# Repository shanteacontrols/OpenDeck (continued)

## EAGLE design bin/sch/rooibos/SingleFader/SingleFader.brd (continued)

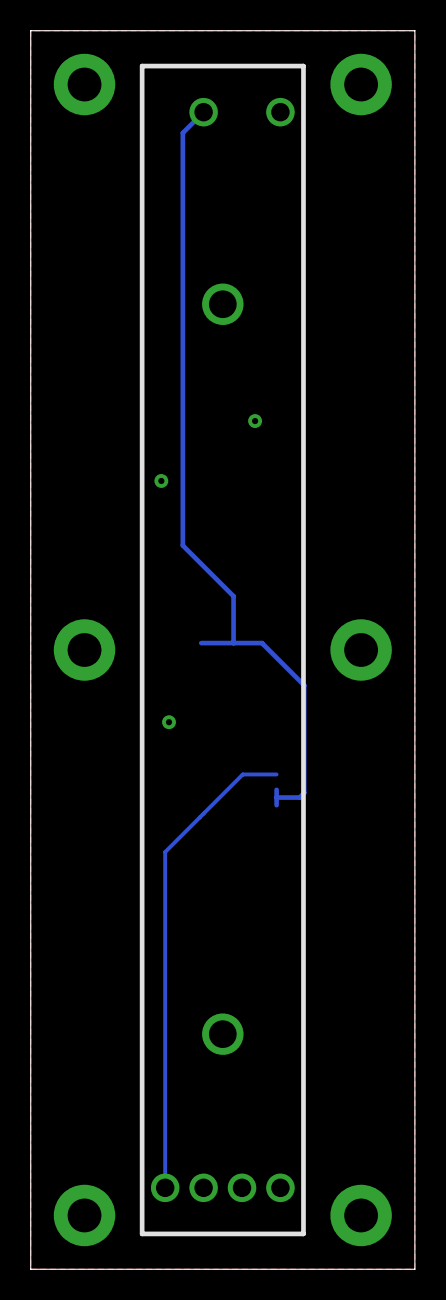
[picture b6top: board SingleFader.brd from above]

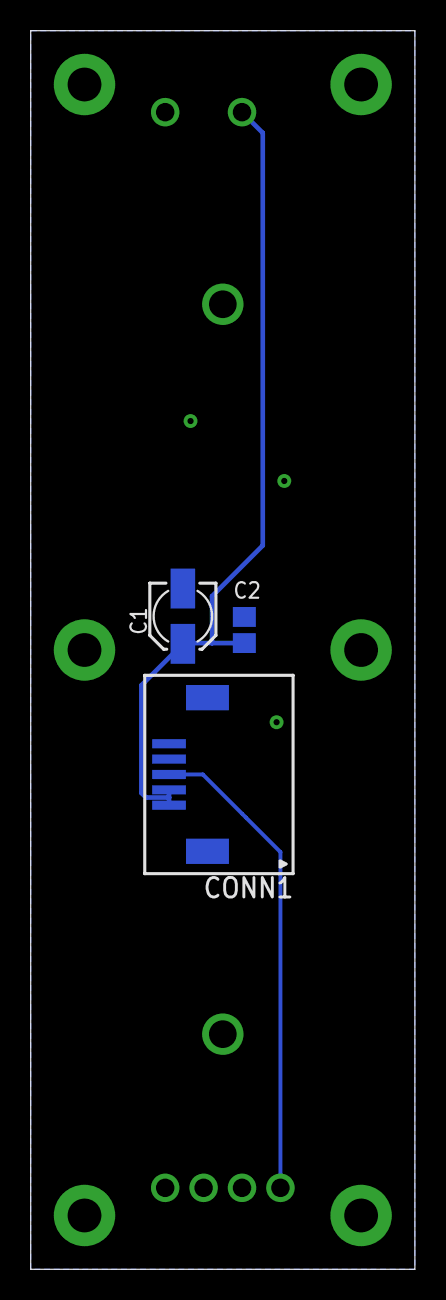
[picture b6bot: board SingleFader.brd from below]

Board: 2 copper layers, 25.0 x 80.6 mm, 4 parts (3 on the bottom side), 3 nets.

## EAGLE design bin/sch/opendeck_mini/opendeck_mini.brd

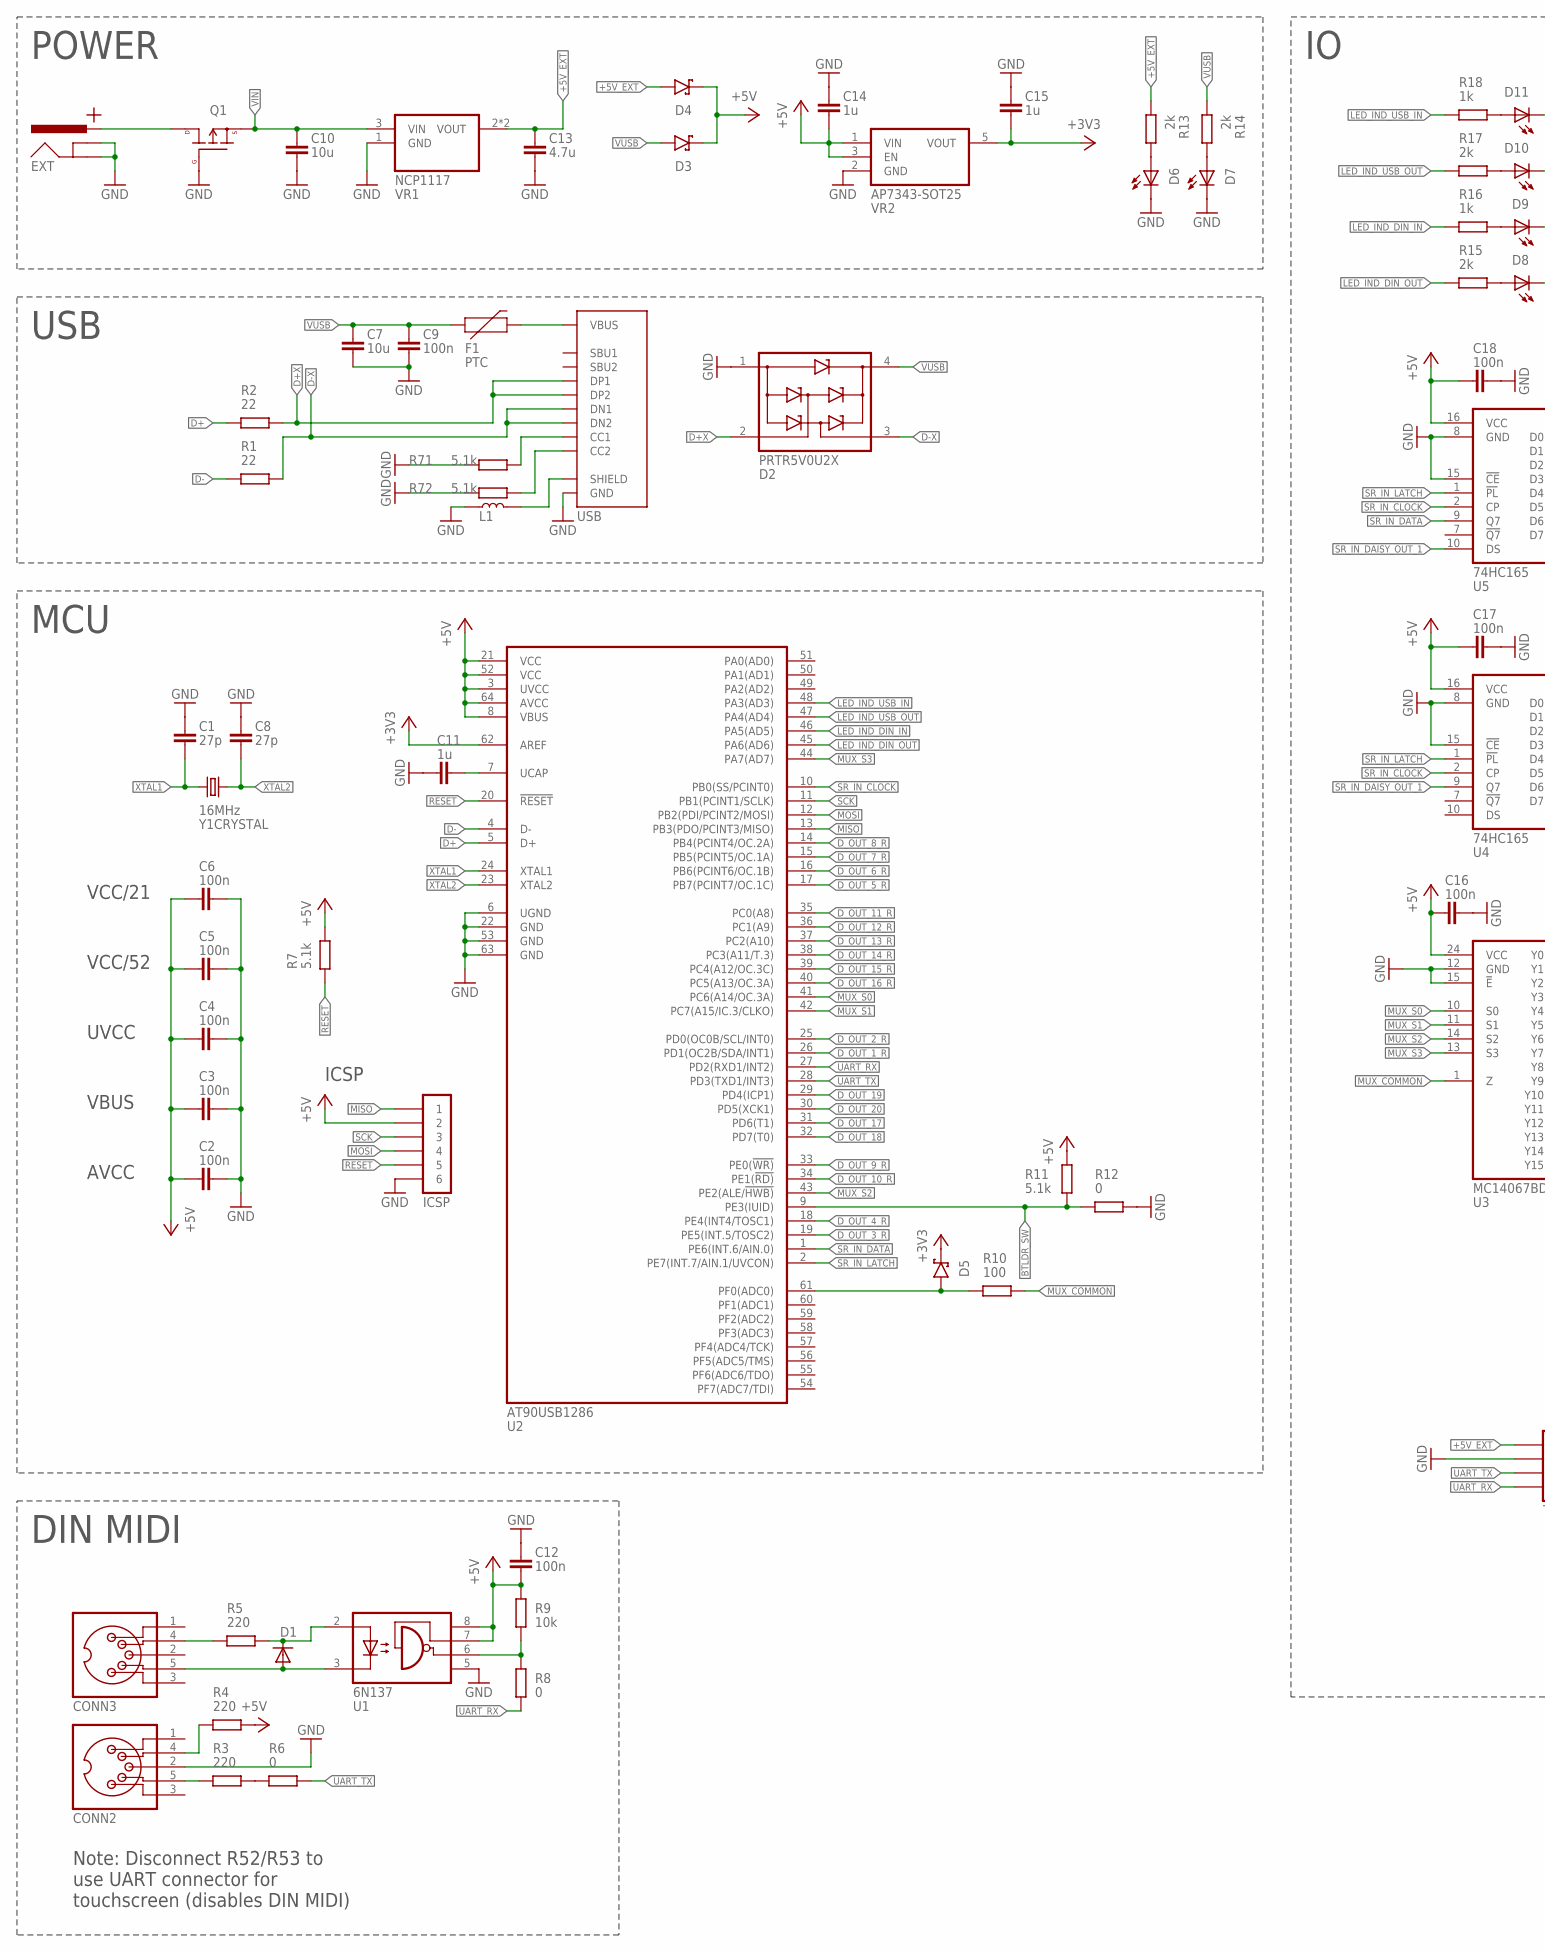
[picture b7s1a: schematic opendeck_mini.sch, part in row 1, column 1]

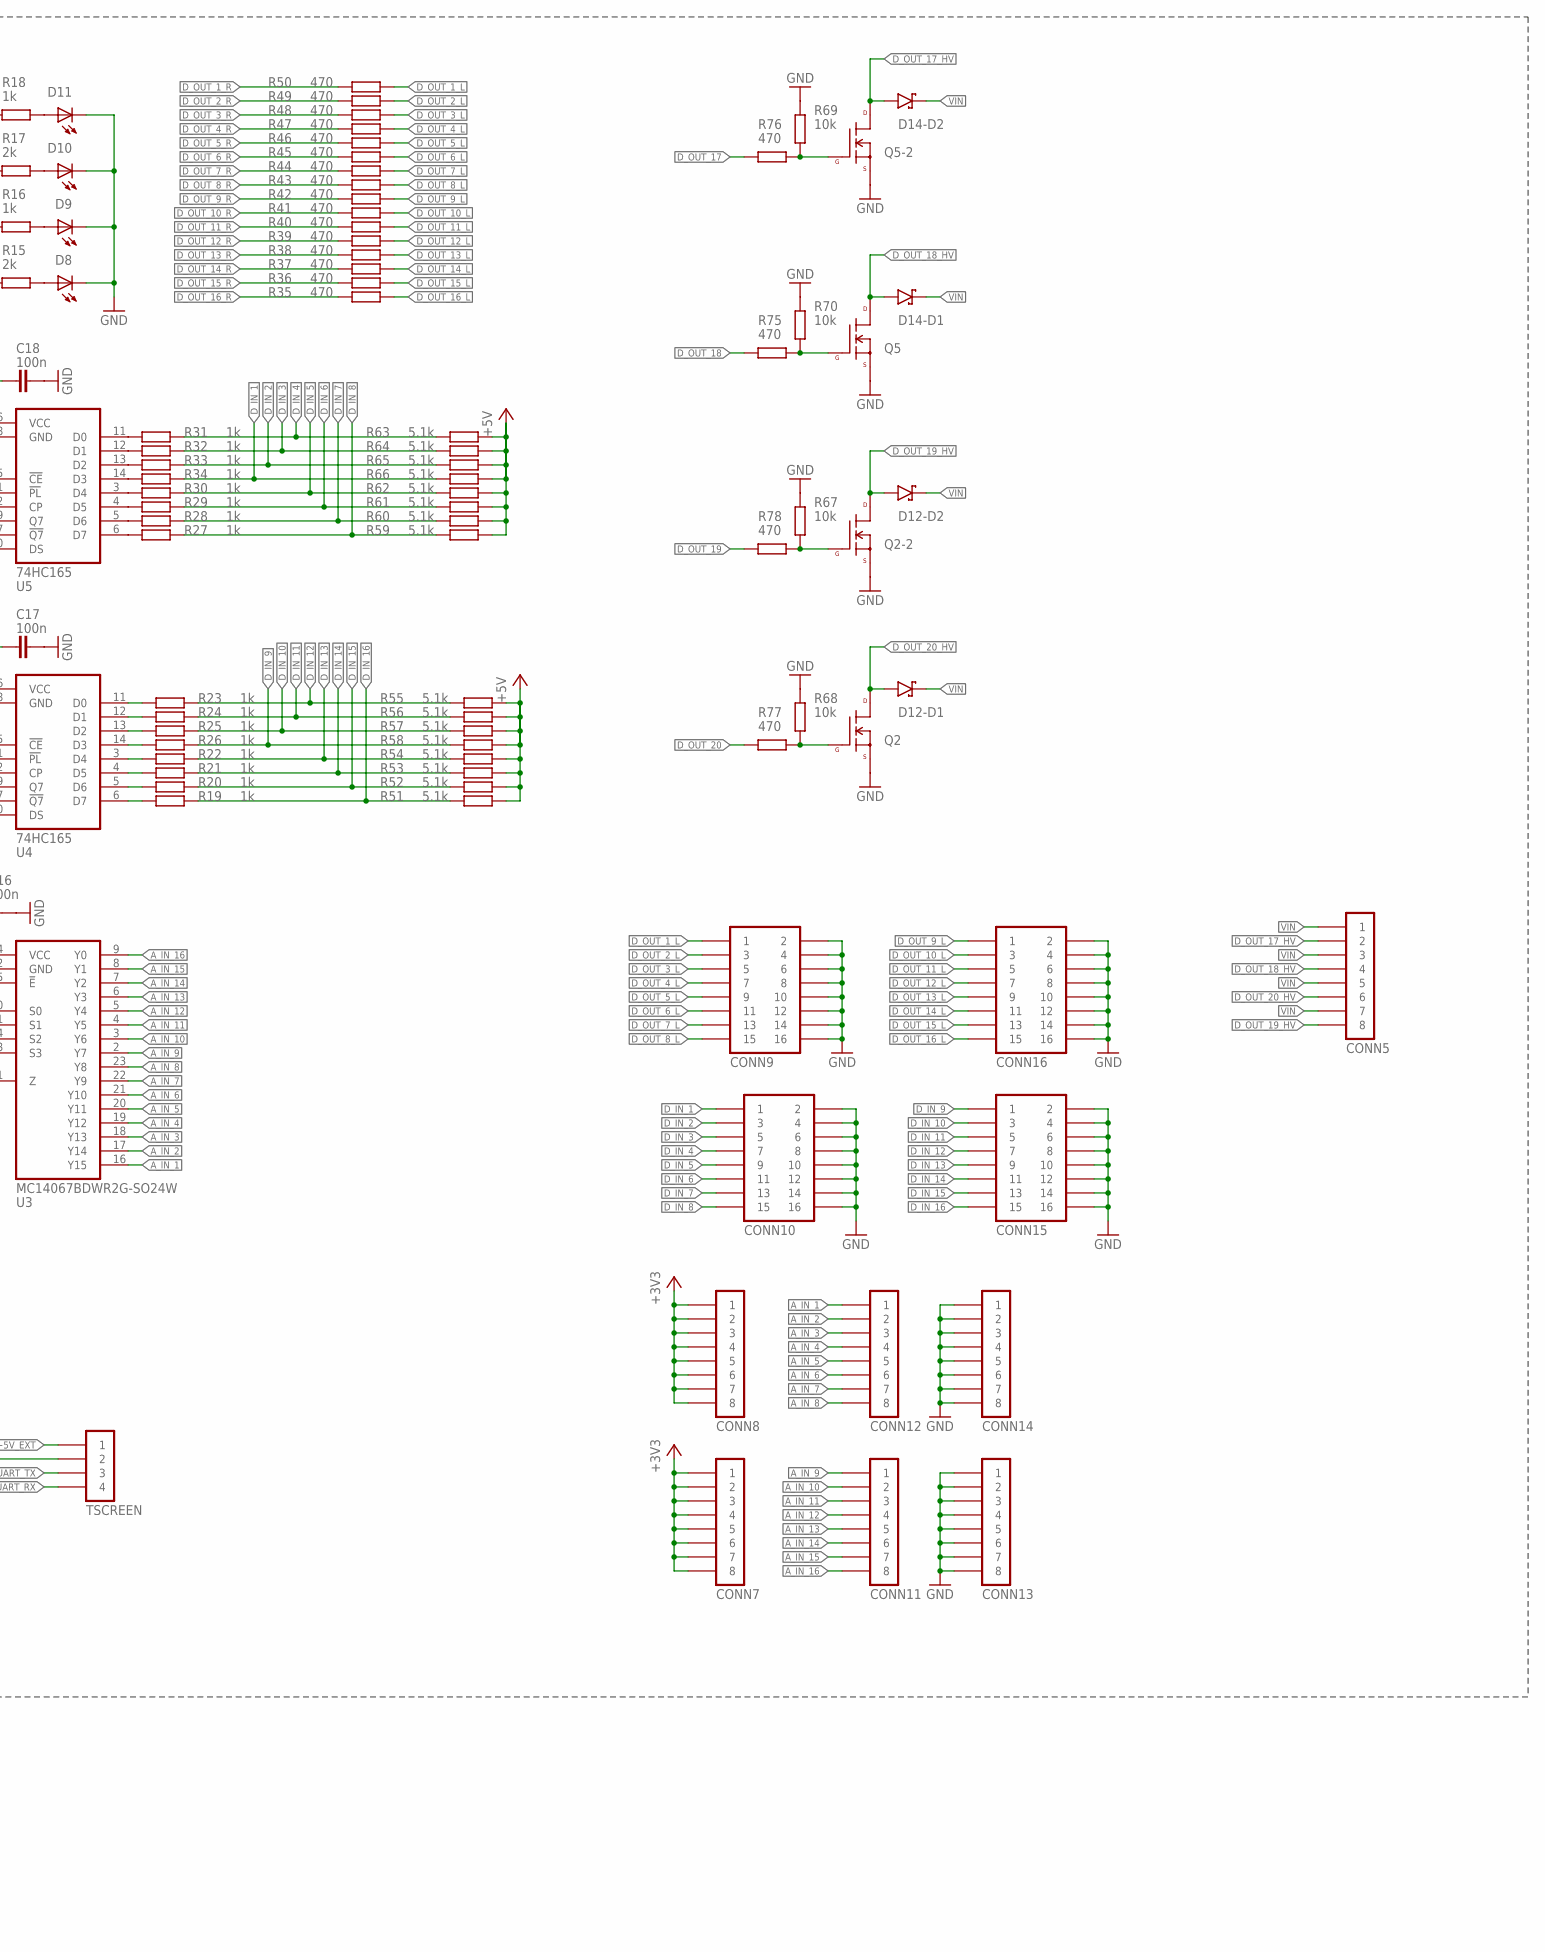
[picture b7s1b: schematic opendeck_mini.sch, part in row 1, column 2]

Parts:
C1, C8: 27p; C0402
C2, C3, C4, C5, C6, C9, C12, C16, C17, C18: 100n; C0402
C7, C10: 10u; C0805
C11, C14, C15: 1u; C0603
C13: 4.7u; C0603
CONN2, CONN3: MIDI_CONN-STD; DIN5
CONN5: PINHD-1X08; PHOENIX_CONTACT-1984675
CONN7, CONN8, CONN11, CONN12, CONN13, CONN14: PINHD-1X08-TH-2.54MM; 1X08-2.54
CONN9, CONN10, CONN15, CONN16: PINHD-2X08-TH-2.54MM; 2X08-2.54
D1: 1N4148; SOD-323
D2: PRTR5V0U2X; SOT143
D3, D4: BAT46INFEON-SOD123; SOD-123
D5: BAT46-SOT23; SOT23
D6: Green; 0805_LED
D7: Blue; 0805_LED
D8, D10: Red; 0805_LED
D9, D11: Yellow; 0805_LED
D12, D14: BAS7007E6327HTSA1; SOT143
EXT: BARREL_JACK
F1: PTC; L1812
ICSP: PINHD-2X03-TH-2.54MM-V; 2X03-2.54-V
L1: FERRITE_BEAD-BLM21PG221SN1D; L0805
Q1: BSS314PEH6327XTSA1; SOT23
Q2, Q5: NTGD3148N; TSOP-6
R1, R2: 22; R0402
R3, R4, R5: 220; R0402
R6, R8, R12: 0; 1X02-2.54-V
R7, R11, R51, R52, R53, R54, R55, R56, R57, R58, R59, R60, R61, R62, R63, R64, R65, R66, R71, R72: 5.1k; R0402
R9, R67, R68, R69, R70: 10k; R0402
R10: 100; R0402
R13, R14, R15, R17: 2k; R0402
R16, R18, R19, R20, R21, R22, R23, R24, R25, R26, R27, R28, R29, R30, R31, R32, R33, R34: 1k; R0402
R35, R36, R37, R38, R39, R40, R41, R42, R43, R44, R45, R46, R47, R48, R49, R50, R75, R76, R77, R78: 470; R0402
TSCREEN: PINHD-1X04-TH-2.54MM; 1X04-2.54
U1: 6N137; DIL08
U2: AT90USB1286; TQFP-64-14X14
U3: MC14067BDWR2G-SO24W; SO24-W
U4, U5: 74HC165; SO16
USB: USB-C; GCT-USB4085-GF-A
VR1: NCP1117; SOT223
VR2: AP7343-SOT25; SOT25
Y1: 16MHz; CRYSTAL-SMD-3.2X2.5

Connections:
+3V3: C15.2, CONN7.1, CONN7.2, CONN7.3, CONN7.4, CONN7.5, CONN7.6, CONN7.7, CONN7.8, CONN8.1, CONN8.2, CONN8.3, CONN8.4, CONN8.5, CONN8.6, CONN8.7, CONN8.8, D5.3 (C), U2.62 (AREF), VR2.5 (VOUT)
+5V: C2.1, C3.1, C4.1, C5.1, C6.1, C12.2, C14.2, C16.1, C17.1, C18.1, D3.C, D4.C, ICSP.2, R4.2, R7.2, R9.2, R11.2, R51.2, R52.2, R53.2, R54.2, R55.2, R56.2, R57.2, R58.2, R59.2, R60.2, R61.2, R62.2, R63.2, R64.2, R65.2, R66.2, U1.7 (VE), U1.8 (VCC), U2.3 (UVCC), U2.8 (VBUS), U2.21 (VCC), U2.52 (VCC), U2.64 (AVCC), U3.24 (VCC), U4.16 (VCC), U5.16 (VCC), VR2.1 (VIN), VR2.3 (EN)
+5V_EXT: C13.1, D4.A, R13.1, TSCREEN.1, VR1.2 (VOUT), VR1.4 (VOUT)
A_IN_1: CONN12.1, U3.16 (Y15)
A_IN_2: CONN12.2, U3.17 (Y14)
A_IN_3: CONN12.3, U3.18 (Y13)
A_IN_4: CONN12.4, U3.19 (Y12)
A_IN_5: CONN12.5, U3.20 (Y11)
A_IN_6: CONN12.6, U3.21 (Y10)
A_IN_7: CONN12.7, U3.22 (Y9)
A_IN_8: CONN12.8, U3.23 (Y8)
A_IN_9: CONN11.1, U3.2 (Y7)
A_IN_10: CONN11.2, U3.3 (Y6)
A_IN_11: CONN11.3, U3.4 (Y5)
A_IN_12: CONN11.4, U3.5 (Y4)
A_IN_13: CONN11.5, U3.6 (Y3)
A_IN_14: CONN11.6, U3.7 (Y2)
A_IN_15: CONN11.7, U3.8 (Y1)
A_IN_16: CONN11.8, U3.9 (Y0)
BTLDR_SW: R11.1, R12.1, U2.9 (PE3(IUID))
D+: R2.1, U2.5 (D+)
D+X: D2.2 (I/O1), R2.2, USB.A6 (DP1), USB.B6 (DP2)
D-: R1.1, U2.4 (D-)
D-X: D2.3 (I/O2), R1.2, USB.A7 (DN1), USB.B7 (DN2)
D_IN_1: CONN10.1, R34.2, R66.1
D_IN_2: CONN10.3, R33.2, R65.1
D_IN_3: CONN10.5, R32.2, R64.1
D_IN_4: CONN10.7, R31.2, R63.1
D_IN_5: CONN10.9, R30.2, R62.1
D_IN_6: CONN10.11, R29.2, R61.1
D_IN_7: CONN10.13, R28.2, R60.1
D_IN_8: CONN10.15, R27.2, R59.1
D_IN_9: CONN15.1, R26.2, R58.1
D_IN_10: CONN15.3, R25.2, R57.1
D_IN_11: CONN15.5, R24.2, R56.1
D_IN_12: CONN15.7, R23.2, R55.1
D_IN_13: CONN15.9, R22.2, R54.1
D_IN_14: CONN15.11, R21.2, R53.1
D_IN_15: CONN15.13, R20.2, R52.1
D_IN_16: CONN15.15, R19.2, R51.1
D_OUT_1_L: CONN9.1, R50.2
D_OUT_1_R: R50.1, U2.26 (PD1(OC2B/SDA/INT1))
D_OUT_2_L: CONN9.3, R49.2
D_OUT_2_R: R49.1, U2.25 (PD0(OC0B/SCL/INT0))
D_OUT_3_L: CONN9.5, R48.2
D_OUT_3_R: R48.1, U2.19 (PE5(INT.5/TOSC2))
D_OUT_4_L: CONN9.7, R47.2
D_OUT_4_R: R47.1, U2.18 (PE4(INT4/TOSC1))
D_OUT_5_L: CONN9.9, R46.2
D_OUT_5_R: R46.1, U2.17 (PB7(PCINT7/OC.1C))
D_OUT_6_L: CONN9.11, R45.2
D_OUT_6_R: R45.1, U2.16 (PB6(PCINT6/OC.1B))
D_OUT_7_L: CONN9.13, R44.2
D_OUT_7_R: R44.1, U2.15 (PB5(PCINT5/OC.1A))
D_OUT_8_L: CONN9.15, R43.2
D_OUT_8_R: R43.1, U2.14 (PB4(PCINT4/OC.2A))
D_OUT_9_L: CONN16.1, R42.1
D_OUT_9_R: R42.2, U2.33 (PE0(!WR))
D_OUT_10_L: CONN16.3, R41.1
D_OUT_10_R: R41.2, U2.34 (PE1(!RD))
D_OUT_11_L: CONN16.5, R40.1
D_OUT_11_R: R40.2, U2.35 (PC0(A8))
D_OUT_12_L: CONN16.7, R39.1
D_OUT_12_R: R39.2, U2.36 (PC1(A9))
D_OUT_13_L: CONN16.9, R38.1
D_OUT_13_R: R38.2, U2.37 (PC2(A10))
D_OUT_14_L: CONN16.11, R37.1
D_OUT_14_R: R37.2, U2.38 (PC3(A11/T.3))
D_OUT_15_L: CONN16.13, R36.1
D_OUT_15_R: R36.2, U2.39 (PC4(A12/OC.3C))
D_OUT_16_L: CONN16.15, R35.1
D_OUT_16_R: R35.2, U2.40 (PC5(A13/OC.3A))
D_OUT_17: R76.1, U2.31 (PD6(T1))
D_OUT_17_HV: CONN5.2, D14.3 (A), Q5.4 (D)
D_OUT_18: R75.1, U2.32 (PD7(T0))
D_OUT_18_HV: CONN5.4, D14.4 (A), Q5.6 (D)
D_OUT_19: R78.1, U2.29 (PD4(ICP1))
D_OUT_19_HV: CONN5.8, D12.3 (A), Q2.4 (D)
D_OUT_20: R77.1, U2.30 (PD5(XCK1))
D_OUT_20_HV: CONN5.6, D12.4 (A), Q2.6 (D)
GND: C1.1, C2.2, C3.2, C4.2, C5.2, C6.2, C7.2, C8.1, C9.2, C10.2, C11.1, C12.1, C13.2, C14.1, C15.1, C16.2, C17.2, C18.2, CONN2.2, CONN9.2, CONN9.4, CONN9.6, CONN9.8, CONN9.10, CONN9.12, CONN9.14, CONN9.16, CONN10.2, CONN10.4, CONN10.6, CONN10.8, CONN10.10, CONN10.12, CONN10.14, CONN10.16, CONN13.1, CONN13.2, CONN13.3, CONN13.4, CONN13.5, CONN13.6, CONN13.7, CONN13.8, CONN14.1, CONN14.2, CONN14.3, CONN14.4, CONN14.5, CONN14.6, CONN14.7, CONN14.8, CONN15.2, CONN15.4, CONN15.6, CONN15.8, CONN15.10, CONN15.12, CONN15.14, CONN15.16, CONN16.2, CONN16.4, CONN16.6, CONN16.8, CONN16.10, CONN16.12, CONN16.14, CONN16.16, D2.1 (GND), D6.C, D7.C, D8.C, D9.C, D10.C, D11.C, EXT.GND@1 (GND), EXT.GND@2 (GNDBREAK), ICSP.6, L1.1, Q1.1 (G), Q2.2 (S), Q2.5 (S), Q5.2 (S), Q5.5 (S), R12.2, R67.2, R68.2, R69.2, R70.2, R71.1, R72.1, TSCREEN.2, U1.5 (GND), U2.6 (UGND), U2.22 (GND), U2.53 (GND), U2.63 (GND), U3.12 (GND), U3.15 (!E), U4.8 (GND), U4.15 (!CE), U5.8 (GND), U5.15 (!CE), USB.A1 (GND), USB.A12 (GND), USB.B1 (GND), USB.B12 (GND), VR1.1 (GND), VR2.2 (GND)
LED_IND_DIN_IN: R16.1, U2.46 (PA5(AD5))
LED_IND_DIN_OUT: R15.1, U2.45 (PA6(AD6))
LED_IND_USB_IN: R18.1, U2.48 (PA3(AD3))
LED_IND_USB_OUT: R17.1, U2.47 (PA4(AD4))
MISO: ICSP.1, U2.13 (PB3(PDO/PCINT3/MISO))
MOSI: ICSP.4, U2.12 (PB2(PDI/PCINT2/MOSI))
MUX_COMMON: R10.2, U3.1 (Z)
MUX_S0: U2.41 (PC6(A14/OC.3A)), U3.10 (S0)
MUX_S1: U2.42 (PC7(A15/IC.3/CLKO)), U3.11 (S1)
MUX_S2: U2.43 (PE2(ALE/!HWB)), U3.14 (S2)
MUX_S3: U2.44 (PA7(AD7)), U3.13 (S3)
unnamed: CONN3.4, R5.1
unnamed: F1.2, USB.A4 (VBUS), USB.A9 (VBUS), USB.B4 (VBUS), USB.B9 (VBUS)
unnamed: D1.C, R5.2, U1.2 (A)
unnamed: CONN3.5, D1.A, U1.3 (C)
unnamed: CONN2.4, R4.1
unnamed: CONN2.5, R3.1
unnamed: R3.2, R6.1
unnamed: R34.1, U5.14 (D3)
unnamed: R33.1, U5.13 (D2)
unnamed: R32.1, U5.12 (D1)
unnamed: D11.A, R18.2
unnamed: D10.A, R17.2
unnamed: D9.A, R16.2
unnamed: D8.A, R15.2
unnamed: R31.1, U5.11 (D0)
unnamed: R30.1, U5.3 (D4)
unnamed: R29.1, U5.4 (D5)
unnamed: R28.1, U5.5 (D6)
unnamed: R27.1, U5.6 (D7)
unnamed: D5.1 (A), R10.1, U2.61 (PF0(ADC0))
unnamed: D6.A, R13.2
unnamed: D7.A, R14.2
unnamed: R8.2, R9.1, U1.6 (VO)
unnamed: Q5.1 (G), R70.1, R75.2
unnamed: Q5.3 (G), R69.1, R76.2
unnamed: Q2.1 (G), R68.1, R77.2
unnamed: EXT.PWR1 (PWR), Q1.2 (S)
unnamed: R71.2, USB.A5 (CC1)
unnamed: Q2.3 (G), R67.1, R78.2
unnamed: L1.2, USB.P1 (SHIELD), USB.P2 (SHIELD), USB.P3 (SHIELD), USB.P4 (SHIELD)
unnamed: R72.2, USB.B5 (CC2)
unnamed: R26.1, U4.14 (D3)
unnamed: R25.1, U4.13 (D2)
unnamed: R24.1, U4.12 (D1)
unnamed: R23.1, U4.11 (D0)
unnamed: R22.1, U4.3 (D4)
unnamed: R21.1, U4.4 (D5)
unnamed: R20.1, U4.5 (D6)
unnamed: R19.1, U4.6 (D7)
RESET: ICSP.5, R7.1, U2.20 (!RESET)
SCK: ICSP.3, U2.11 (PB1(PCINT1/SCLK))
SR_IN_CLOCK: U2.10 (PB0(SS/PCINT0)), U4.2 (CP), U5.2 (CP)
SR_IN_DAISY_OUT_1: U4.9 (Q7), U5.10 (DS)
SR_IN_DATA: U2.1 (PE6(INT.6/AIN.0)), U5.9 (Q7)
SR_IN_LATCH: U2.2 (PE7(INT.7/AIN.1/UVCON)), U4.1 (!PL), U5.1 (!PL)
UART_RX: R8.1, TSCREEN.4, U2.27 (PD2(RXD1/INT2))
UART_TX: R6.2, TSCREEN.3, U2.28 (PD3(TXD1/INT3))
UCAP: C11.2, U2.7 (UCAP)
VIN: C10.1, CONN5.1, CONN5.3, CONN5.5, CONN5.7, D12.1 (C), D12.2 (C), D14.1 (C), D14.2 (C), Q1.3 (D), VR1.3 (VIN)
VUSB: C7.1, C9.1, D2.4 (VCC), D3.A, F1.1, R14.1
XTAL1: C1.2, U2.24 (XTAL1), Y1.1
XTAL2: C8.2, U2.23 (XTAL2), Y1.3 (2)

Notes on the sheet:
VCC/21
VCC/52
UVCC
VBUS
AVCC
POWER
USB
ICSP
MCU
DIN MIDI
Note: Disconnect R52/R53 to use UART connector for touchscreen (disables DIN MIDI)

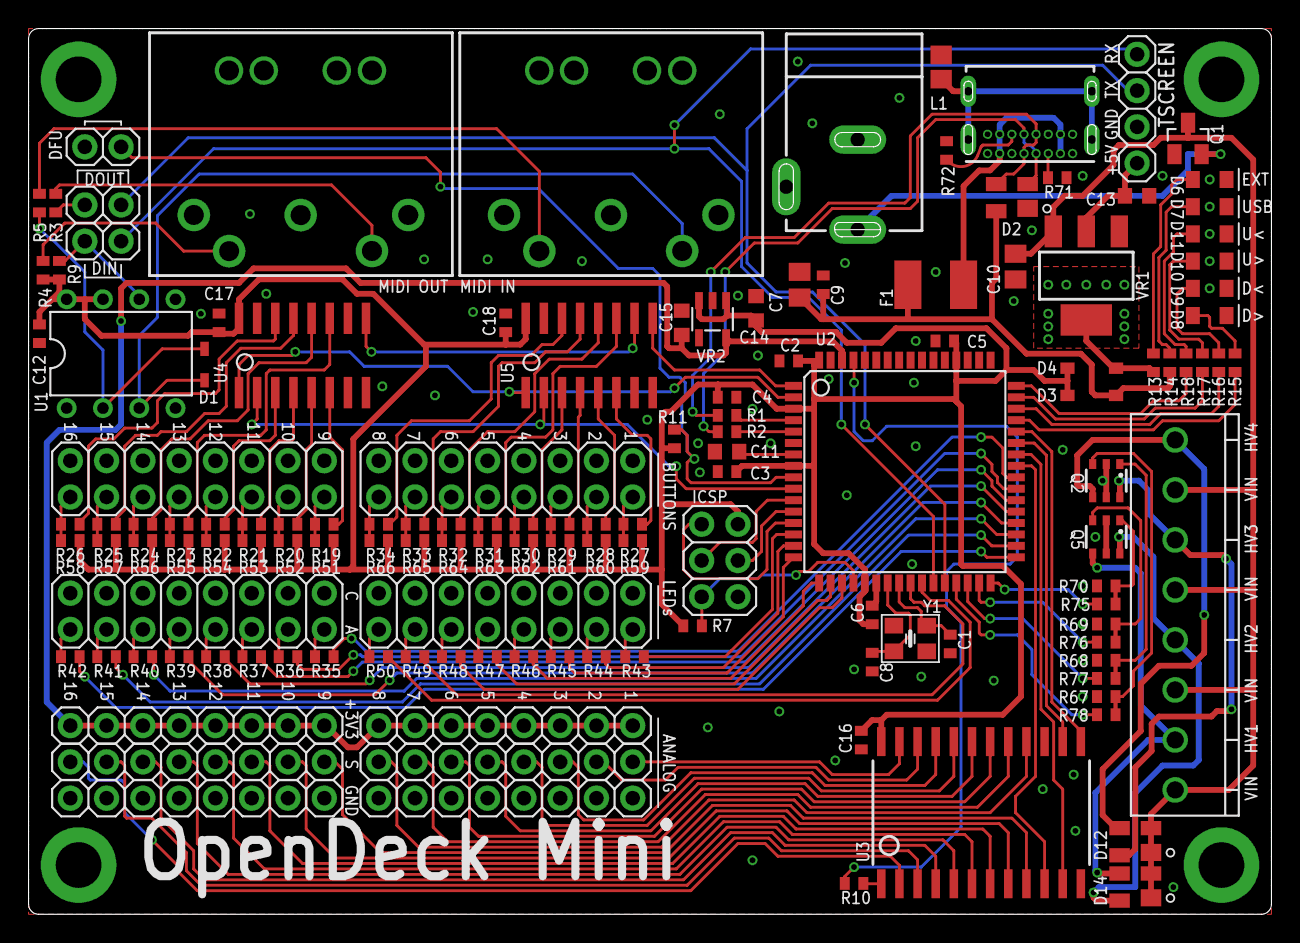
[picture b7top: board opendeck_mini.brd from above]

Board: 2 copper layers, 87.0 x 62.0 mm, 136 parts (0 on the bottom side), 144 nets.

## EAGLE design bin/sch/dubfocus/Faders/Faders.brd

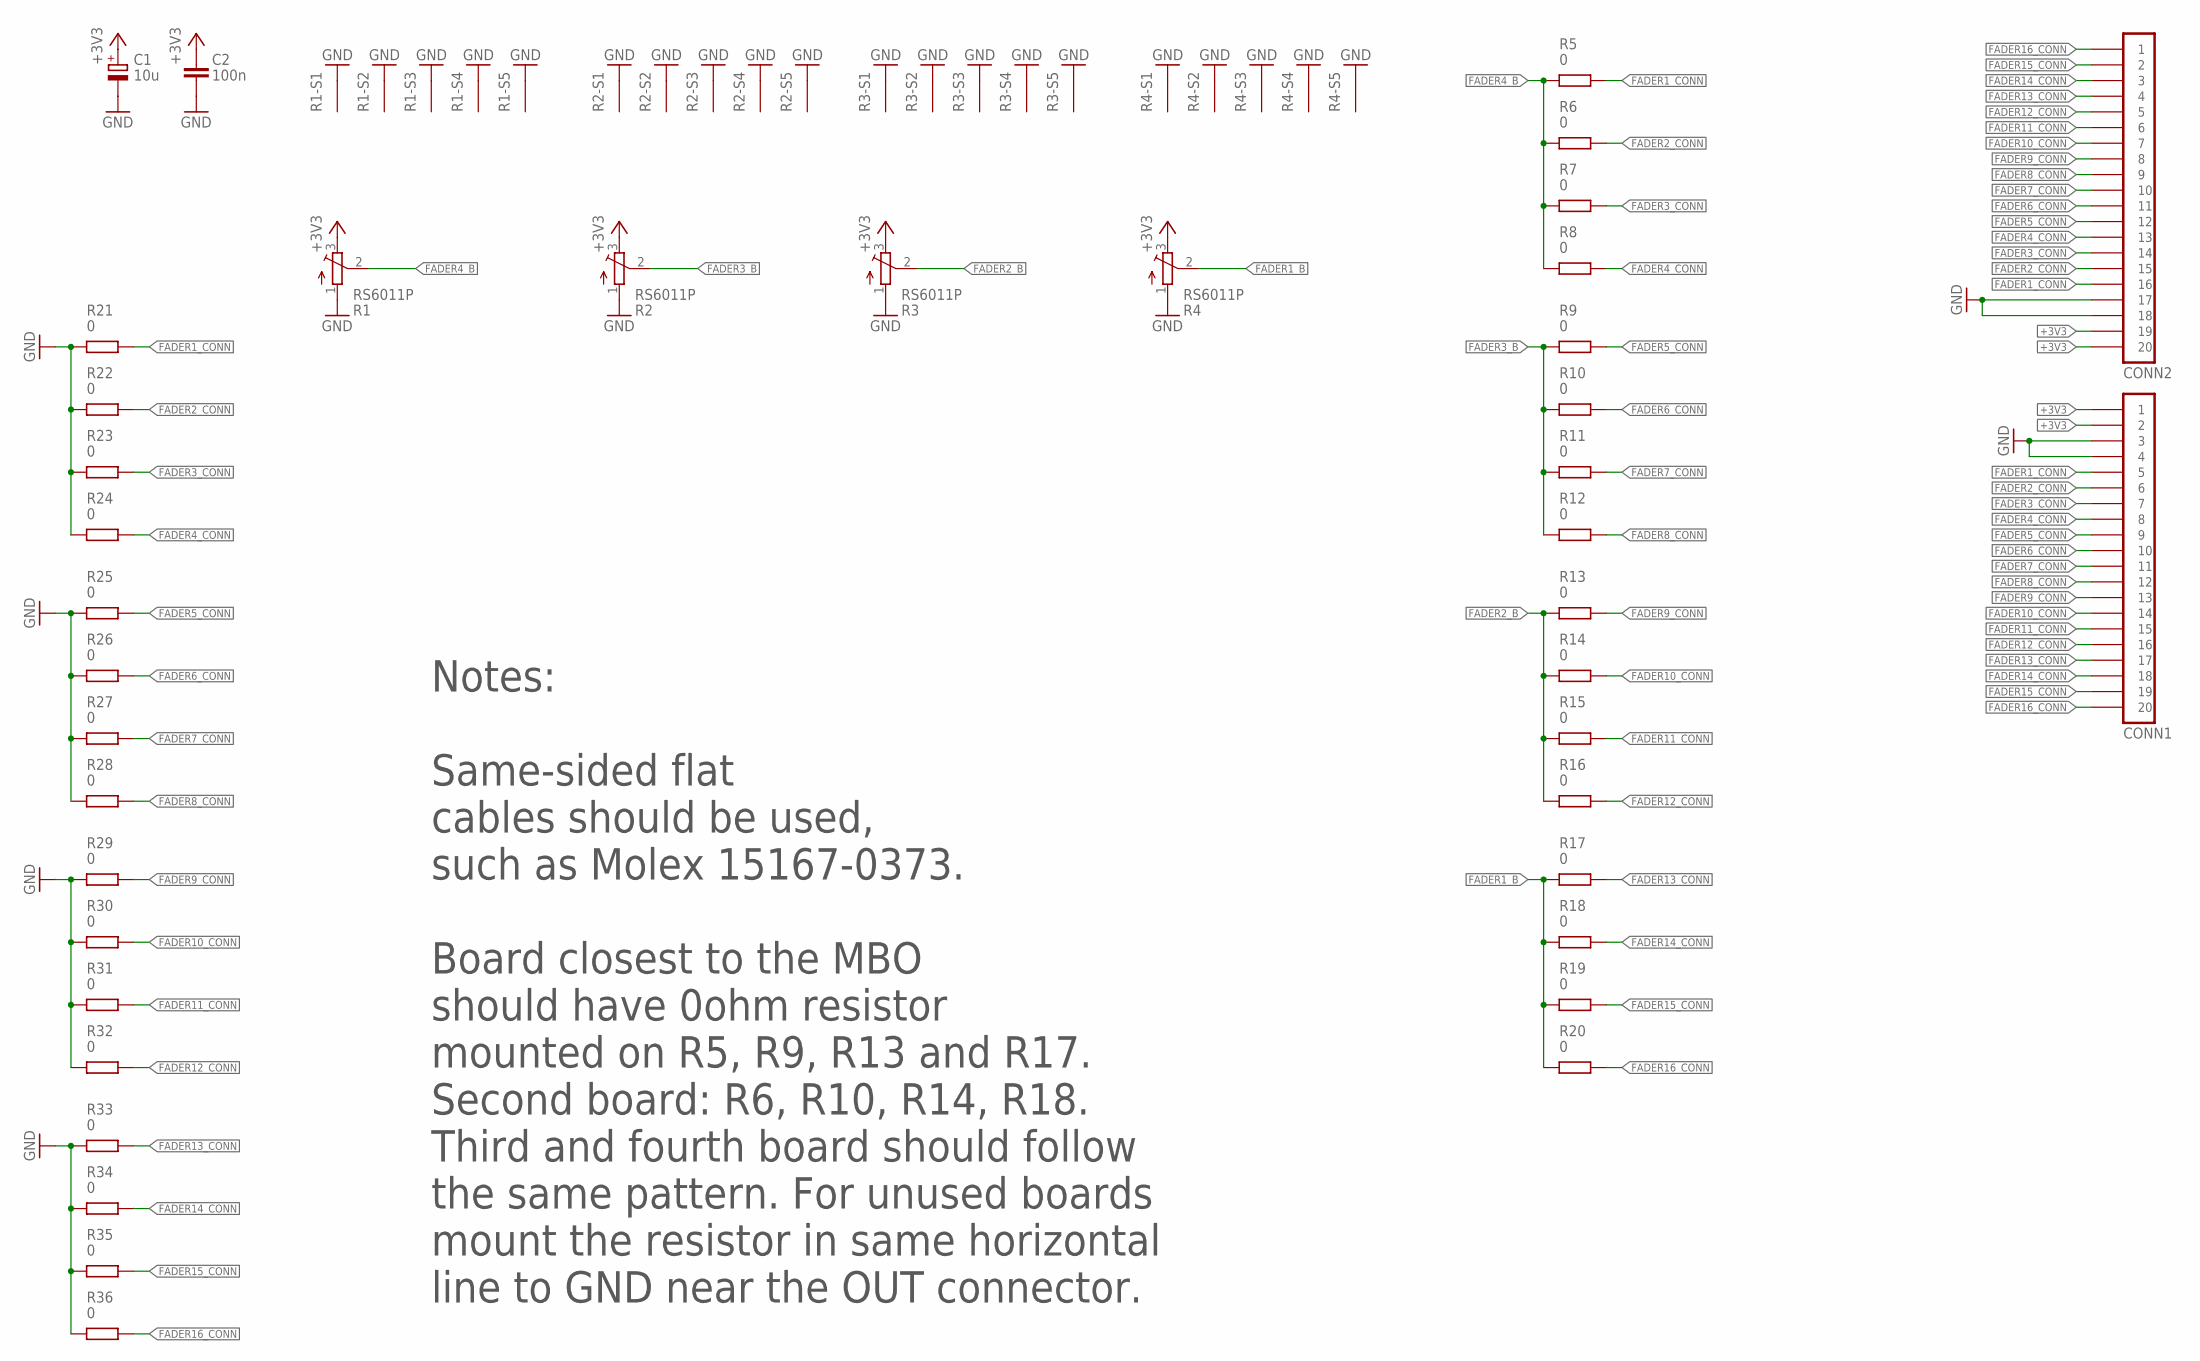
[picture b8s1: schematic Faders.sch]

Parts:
C1: 10u; C-TH-E-0401
C2: 100n; C0805
CONN1, CONN2: PINHD-1X20-SMD; MOLEX-52271-2079
R1, R2, R3, R4: RS6011P; RS6011*P
R5, R6, R7, R8, R9, R10, R11, R12, R13, R14, R15, R16, R17, R18, R19, R20, R21, R22, R23, R24, R25, R26, R27, R28, R29, R30, R31, R32, R33, R34, R35, R36: 0; R0805

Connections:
+3V3: C1.+, C2.1, CONN1.1, CONN1.2, CONN2.19, CONN2.20, R1.3, R2.3, R3.3, R4.3
FADER1_B: R4.2, R17.1, R18.1, R19.1, R20.1
FADER1_CONN: CONN1.5, CONN2.16, R5.2, R21.2
FADER2_B: R3.2, R13.1, R14.1, R15.1, R16.1
FADER2_CONN: CONN1.6, CONN2.15, R6.2, R22.2
FADER3_B: R2.2, R9.1, R10.1, R11.1, R12.1
FADER3_CONN: CONN1.7, CONN2.14, R7.2, R23.2
FADER4_B: R1.2, R5.1, R6.1, R7.1, R8.1
FADER4_CONN: CONN1.8, CONN2.13, R8.2, R24.2
FADER5_CONN: CONN1.9, CONN2.12, R9.2, R25.2
FADER6_CONN: CONN1.10, CONN2.11, R10.2, R26.2
FADER7_CONN: CONN1.11, CONN2.10, R11.2, R27.2
FADER8_CONN: CONN1.12, CONN2.9, R12.2, R28.2
FADER9_CONN: CONN1.13, CONN2.8, R13.2, R29.2
FADER10_CONN: CONN1.14, CONN2.7, R14.2, R30.2
FADER11_CONN: CONN1.15, CONN2.6, R15.2, R31.2
FADER12_CONN: CONN1.16, CONN2.5, R16.2, R32.2
FADER13_CONN: CONN1.17, CONN2.4, R17.2, R33.2
FADER14_CONN: CONN1.18, CONN2.3, R18.2, R34.2
FADER15_CONN: CONN1.19, CONN2.2, R19.2, R35.2
FADER16_CONN: CONN1.20, CONN2.1, R20.2, R36.2
GND: C1.-, C2.2, CONN1.3, CONN1.4, CONN2.17, CONN2.18, R1.1, R1.S1 (S), R1.S2 (S), R1.S3 (S), R1.S4 (S), R1.S5 (S), R2.1, R2.S1 (S), R2.S2 (S), R2.S3 (S), R2.S4 (S), R2.S5 (S), R3.1, R3.S1 (S), R3.S2 (S), R3.S3 (S), R3.S4 (S), R3.S5 (S), R4.1, R4.S1 (S), R4.S2 (S), R4.S3 (S), R4.S4 (S), R4.S5 (S), R21.1, R22.1, R23.1, R24.1, R25.1, R26.1, R27.1, R28.1, R29.1, R30.1, R31.1, R32.1, R33.1, R34.1, R35.1, R36.1

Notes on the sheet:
Notes: Same-sided flat cables should be used, such as Molex 15167-0373. Board closest to the MBO should have 0ohm resistor mounted on R5, R9, R13 and R17. Second board: R6, R10, R14, R18. Third and fourth board should follow the same pattern. For unused boards mount the resistor in same horizontal 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

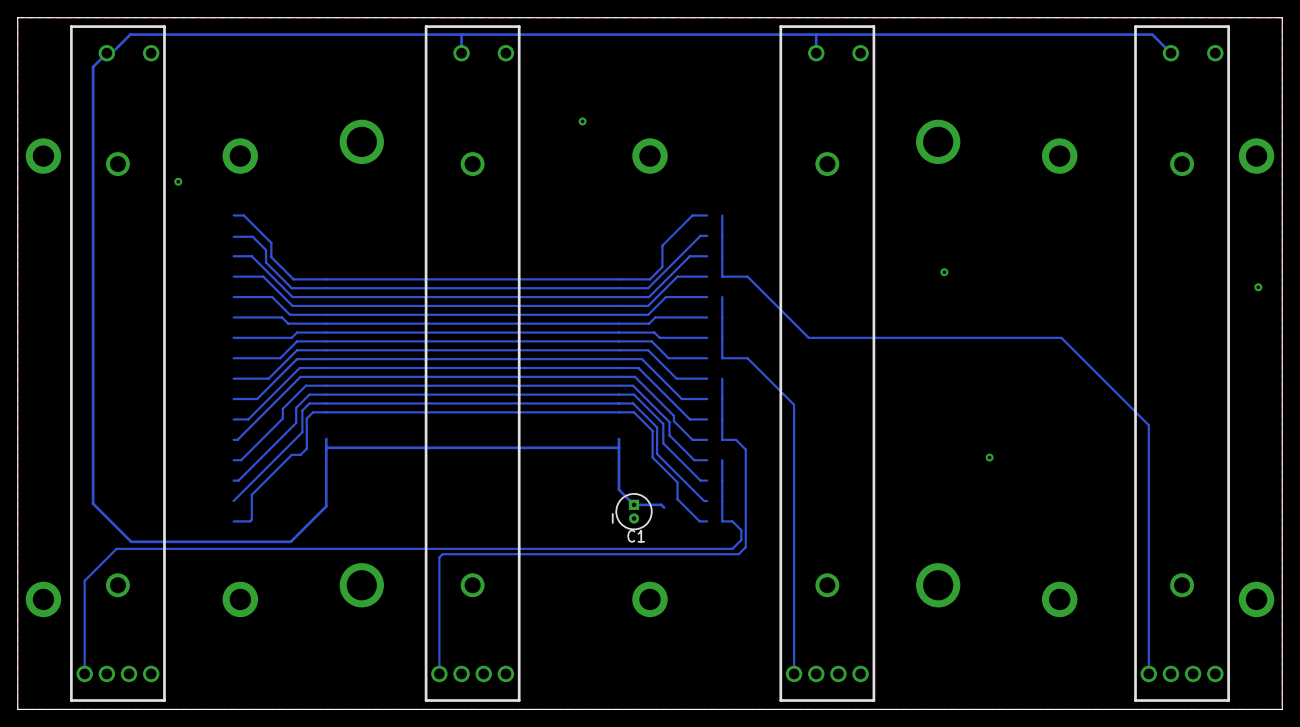
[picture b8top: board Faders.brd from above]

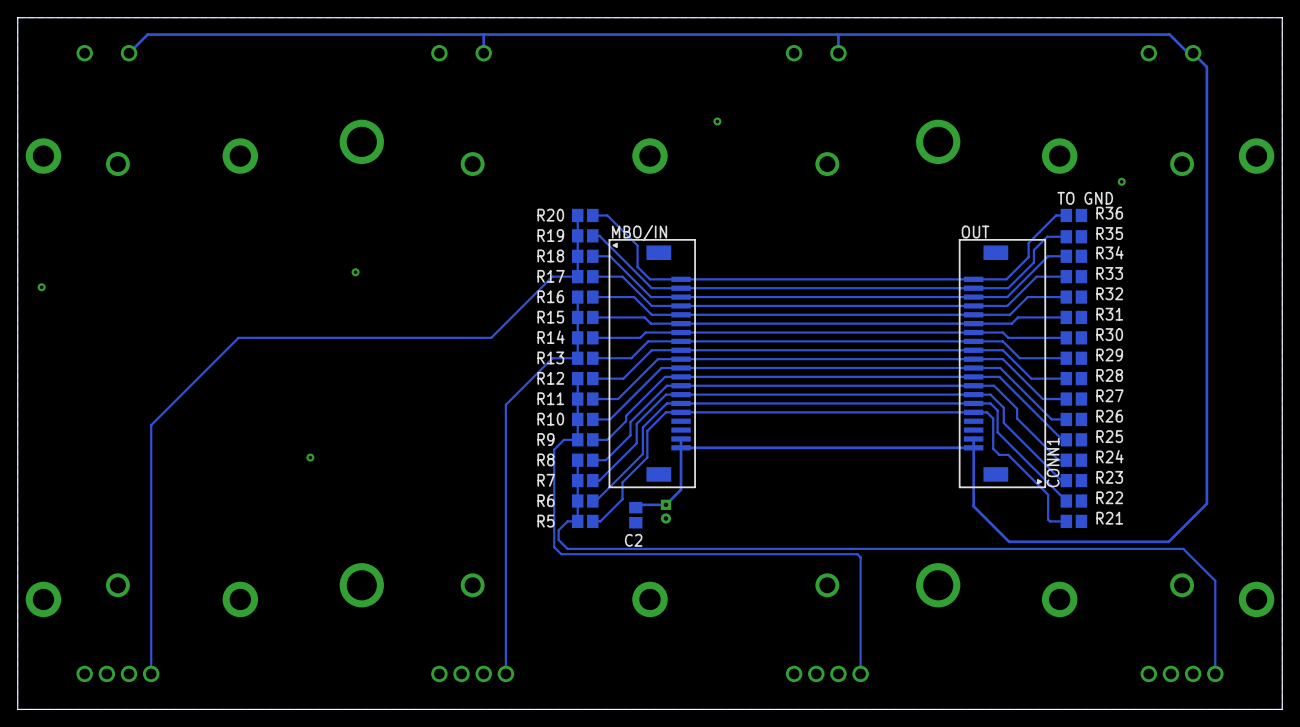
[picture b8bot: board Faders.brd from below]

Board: 2 copper layers, 142.6 x 78.0 mm, 40 parts (35 on the bottom side), 22 nets.

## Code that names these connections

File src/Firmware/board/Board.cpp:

/*
    OpenDeck MIDI platform firmware
    Copyright (C) 2015, 2016 Igor Petrovic

    This program is free software: you can redistribute it and/or modify
    it under the terms of the GNU General Public License as published by
    the Free Software Foundation, either version 3 of the License, or
    (at your option) any later version.

    This program is distributed in the hope that it will be useful,
    but WITHOUT ANY WARRANTY; without even the implied warranty of
    MERCHANTABILITY or FITNESS FOR A PARTICULAR PURPOSE.  See the
    GNU General Public License for more details.

    You should have received a copy of the GNU General Public License
    along with this program.  If not, see <http://www.gnu.org/licenses/>.
*/

#include "Board.h"
#include <util/delay.h>
#include <avr/cpufunc.h>
#include <avr/wdt.h>
#include <avr/eeprom.h>

Board::Board()
{
    //default constructor
}

void Board::init()
{
    cli();
    //disable watchdog
    MCUSR &= ~(1 << WDRF);
    wdt_disable();
    initPins();
    initAnalog();
    initEncoders();

    _delay_ms(5);

    configureTimers();

    //enable global interrupts
    sei();
}

void Board::initPins()
{
    //configure input matrix
    //shift register
    setInput(SR_DIN_PORT, SR_DIN_PIN);
    setOutput(SR_CLK_PORT, SR_CLK_PIN);
    setOutput(SR_LATCH_PORT, SR_LATCH_PIN);

    //decoder
    setOutput(DEC_DM_A0_PORT, DEC_DM_A0_PIN);
    setOutput(DEC_DM_A1_PORT, DEC_DM_A1_PIN);
    setOutput(DEC_DM_A1_PORT, DEC_DM_A2_PIN);

    //configure led matrix
    //rows

    setHigh(LED_ROW_1_PORT, LED_ROW_1_PIN);
    setHigh(LED_ROW_2_PORT, LED_ROW_2_PIN);
    setHigh(LED_ROW_3_PORT, LED_ROW_3_PIN);
    setHigh(LED_ROW_4_PORT, LED_ROW_4_PIN);
    setHigh(LED_ROW_5_PORT, LED_ROW_5_PIN);
    setHigh(LED_ROW_6_PORT, LED_ROW_6_PIN);

    setOutput(LED_ROW_1_PORT, LED_ROW_1_PIN);
    setOutput(LED_ROW_2_PORT, LED_ROW_2_PIN);
    setOutput(LED_ROW_3_PORT, LED_ROW_3_PIN);
    setOutput(LED_ROW_4_PORT, LED_ROW_4_PIN);
    setOutput(LED_ROW_5_PORT, LED_ROW_5_PIN);
    setOutput(LED_ROW_6_PORT, LED_ROW_6_PIN);

    //decoder
    setOutput(DEC_LM_A0_PORT, DEC_LM_A0_PIN);
    setOutput(DEC_LM_A1_PORT, DEC_LM_A1_PIN);
    setOutput(DEC_LM_A2_PORT, DEC_LM_A2_PIN);

    //configure analog
    //select pins
    setOutput(MUX_S0_PORT, MUX_S0_PIN);
    setOutput(MUX_S1_PORT, MUX_S1_PIN);
    setOutput(MUX_S2_PORT, MUX_S2_PIN);
    setOutput(MUX_S3_PORT, MUX_S3_PIN);

    //mux inputs
    setInput(MUX_1_IN_PORT, MUX_1_IN_PIN);
    setInput(MUX_2_IN_PORT, MUX_2_IN_PIN);

    //bootloader led
    setOutput(BTLDR_LED_PORT, BTLDR_LED_PIN);
}

void Board::configureTimers()
{
    //clear timer0 conf
    TCCR0A = 0;
    TCCR0B = 0;
    TIMSK0 = 0;

    //clear timer1 conf
    TCCR1A = 0;
    TCCR1B = 0;

    //clear timer3 conf
    TCCR3A = 0;
    TCCR3B = 0;

    //clear timer4 conf
    TCCR4A = 0;
    TCCR4B = 0;
    TCCR4C = 0;
    TCCR4D = 0;
    TCCR4E = 0;

    //set timer1, timer3 and timer4 to phase correct pwm mode
    //timer 1
    TCCR1A |= (1<<WGM10);           //phase correct PWM
    TCCR1B |= (1<<CS10);            //prescaler 1
    //timer 3
    TCCR3A |= (1<<WGM30);           //phase correct PWM
    TCCR3B |= (1<<CS30);            //prescaler 1
    //timer 4
    TCCR4A |= (1<<PWM4A);           //Pulse Width Modulator A Enable
    TCCR4B |= (1<<CS40);            //prescaler 1
    TCCR4C |= (1<<PWM4D);           //Pulse Width Modulator D Enable
    TCCR4D |= (1<<WGM40);           //phase correct PWM

    //set timer0 to ctc, used for millis/led matrix
    TCCR0A |= (1<<WGM01);           //CTC mode
    TCCR0B |= (1<<CS01)|(1<<CS00);  //prescaler 64
    OCR0A = 124;                    //500uS
    TIMSK0 |= (1<<OCIE0A);          //compare match interrupt
}

Board board;
